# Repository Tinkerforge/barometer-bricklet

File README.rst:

Barometer Bricklet
==================

This repository contains the firmware source code and the hardware design
files. The documentation generator configs can be found at
https://github.com/Tinkerforge/generators

Repository Content
------------------

software/:
 * examples/: Examples for all supported languages
 * build/: Compiled files
 * src/: Source code of firmware
 * Makefile: Makefile to build project

hardware/:
 * Contains KiCad project files and additionally schematics as PDF

datasheets/:
 * Contains datasheets for sensors and complex ICs that are used

Hardware
--------

The hardware is designed with the open source EDA Suite KiCad
(http://www.kicad.org). Before you are able to open the files,
you have to install the Tinkerforge kicad-libraries
(https://github.com/Tinkerforge/kicad-libraries). You can either clone
them directly in hardware/ or clone them in a separate folder and
symlink them into hardware/
(ln -s kicad_path/kicad-libraries project_path/hardware). After that you
can open the .pro file in hardware/ with KiCad and from there view and
modify the schematics and the PCB layout.

Software
--------

If you want to do your own Brick/Bricklet firmware development we highly
recommend that you use our build environment setup script and read the
tutorial (https://www.tinkerforge.com/en/doc/Tutorials/Tutorial_Build_Environment/Tutorial.html).

To compile the C code we recommend you to install the newest GNU Arm Embedded
Toolchain (https://launchpad.net/gcc-arm-embedded/+download).
You also need to install bricklib (https://github.com/Tinkerforge/bricklib)
and brickletlib (https://github.com/Tinkerforge/brickletlib).

You can either clone it directly in software/src/ or clone it in a
separate folder and symlink it into software/src/
(ln -s bricklib_path/bricklib project_path/software/src/ and
ln -s brickletlib_path/brickletlib project_path/software/src/).
Finally make sure to have CMake installed
(http://www.cmake.org/cmake/resources/software.html).

After that you can build the firmware by invoking make in software/.
The firmware (.bin) can then be found in software/build/ and uploaded
with brickv (click button "Flashing" on start screen).

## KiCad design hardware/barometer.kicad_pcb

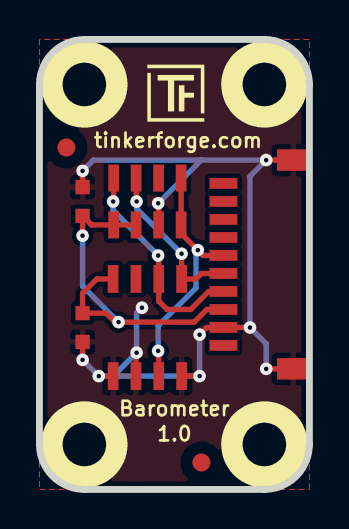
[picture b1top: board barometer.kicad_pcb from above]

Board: 2 copper layers, 15.0 x 25.0 mm, 13 parts (0 on the bottom side), 5 nets.

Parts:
C1, C2: 100nF; C0603
Fiducial_Mark: VAL**; Fiducial_Mark
Fiducial_Mark#2: VAL**; Fiducial_Mark
P1: CON-SENSOR
U1: M24C64; SOIC8
U2: MS5611
U3, U4, U5, U6: DRILL; DRILL_NP
VAL: CE_5mm
VAL#2: WEEE_7mm

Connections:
GND: C1.2, C2.2, P1.2, P1.EP, U1.1, U1.2, U1.4, U2.3
unnamed: P1.6, U1.3, U2.4, U2.5
SCL: P1.4, U1.6, U2.8
SDA: P1.5, U1.5, U2.7
VCC: C1.1, C2.1, P1.3, U1.8, U2.1, U2.2

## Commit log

2012-07-01 Add generate_makefile.bat for windows
2012-08-02 First try to implement calibration readout, not working yet
2012-08-03 Fix I2C communication and add calculation logic
2012-08-03 Remove Eclipse project files
2012-08-06 Apply moving average to air pressure
    Calculate air pressure with 5 extra bits of precision.
2012-08-10 Try to improve altitude calculation
    Simplify temperature to just a getter to make more RAM available.
    Add longer averaging for D1 and D2.
    Use a lookup table for altitude calculation.
2012-09-07 Ignore temporary build files
2012-09-17 update of hardware files
2012-09-28 Update to latest config
2012-09-28 Update datasheet
2012-09-28 Fix moving average calculation for D1 and fix auto calibration
2012-10-01 Replace calibate function with getter/setter for reference air pressure
    This is more flexible and allows to use QNH and QFE values.
2012-10-01 Check CRC4 of PROM data
2012-10-02 Add examples
2012-10-04 Extend .gitignore
2012-10-04 Fix overflow in altitude calculation
2012-10-04 Update changelog
2012-10-05 Update version number
    Missed in last commit.
2012-10-11 Fix sensor readout timings, avoids reading wrong sensor values
2012-10-24 Make cmake find the correct objcopy binary
    On some systems cmake uses the wrong objcopy binary, tell it to use
    the correct one.
2012-11-13 Support for protocol 2.0
2012-11-28 Make python examples protocol 2.0 compatible
2012-11-29 Make Ruby examples Protocol 2.0 compatible
2012-11-29 Make C examples Protocol 2.0 compatible
2012-11-29 Make Java examples Protocol 2.0 compatible
2012-11-29 Make PHP examples Protocol 2.0 compatible
2012-11-29 Make Delphi/Pascal examples Protocol 2.0 compatible
2012-11-30 delphi: Remove unnecessary parentheses and call destructor again
2012-12-05 Add protocol 2.0 compatability to C# bindings
2012-12-06 Fix C examples
2012-12-11 Avoid g++ warnings about missing casts in C examples
2013-01-09 Use specific device object for callbacks
2013-01-17 Make Java examples compatible to new listener approach
2013-01-28 Update outdated comment in Java example
2013-02-07 Use IPconnection disconnect explicitly in examples
2013-02-18 Add Visual Basic .NET examples
2013-03-05 Fix schematic filename
2013-05-14 Add API for configuration of averaging parameters
2013-08-09 Add shell examples
2013-08-21 windows: Don't trigger a build in generate_makefile.bat
    Also use normal make instead of a special named one.
2013-09-23 Fix typo
2013-12-19 Fix wrong length for GetDebounce packet (through brickletlib)
2014-01-10 Add Perl examples
2014-01-15 php: Use const for constant values
2014-02-07 Add Mathematica examples
2014-02-10 perl: fixed namespace
2014-02-11 javascript: adding examples
2014-02-11 javascript: short exmaples
2014-02-18 javascript: examples fixed
2014-02-20 javascript: add html examples
2014-02-24 javascript: port 4280, startExample()
2014-02-28 javascript: Break long lines and cleanup whitespace
2014-03-05 Add LabVIEW examples
2014-03-06 labview: Add examples in LV2010 format
2014-03-25 matlab: add examples
2014-04-02 java: Unify constants style
2014-04-02 perl: Unify print style
2014-04-17 matlab: Adapt examples to new callback style
2014-04-17 matlab: Add parentheses to make pygments happy
2014-04-17 matlab: Fix string in Octave
2014-07-15 java: Replace System.console() usage with an Eclipse compatible pattern
2014-12-02 Use ReadLine instead of ReadKey for C# example
2015-02-13 vbnet: Use ReadLine instead of ReadKey
    Because ReadKey doesn't work with a pipe as stdin on the RED Brick.
2015-03-02 windows: Stop cmake from searching for mingw32-make.exe
    Using MinGW Makefiles as generator makes cmake search for mingw32-make.exe
    which might not be installed because GnuWin32's make.exe is used instead.
2015-03-26 update hardware files of barometer bricklet
2015-04-09 c: Whitespace
2015-06-24 javascript: Cleanup output creation
2015-07-23 Make JavaScript browser example textarea readonly
2015-07-27 Cleanup C/C++, C#, Java, Python and Ruby examples
2015-07-29 Reformat changelog
2015-08-07 Use full device class name in Python examples
2015-08-12 Fix minor warnings in C/C++ examples
2015-08-14 Cleanup Delphi examples
2015-08-18 Cleanup VB.NET examples
2015-08-19 Cleanup Perl examples
2015-08-21 Prefer printf over puts in C/C++ examples
2015-09-09 Duplicate cmake call to fix bug during cmake creation
2015-09-30 Generator based example cleanup
2015-11-12 matlab: Fix callback handling for R2014a
    http://undocumentedmatlab.com/blog/matlab-callbacks-for-java-events-in-r2014a
2015-11-25 Include date and commit into changelog
2016-05-18 c: Add missing device destroy call
2016-07-01 Make the change UID comment more explicit
2016-07-01 Whitespace
2017-04-13 csharp: Adapt example
2017-04-21 shell: Adapt example
2017-06-02 octave: Use javaObject instead of deprecated java_new
2017-08-01 Fix schematic symbols/markings/descriptions
2017-08-01 Add 3d information (final)
2017-08-01 PDF schematic: color instead of b/w
2017-08-01 Add 3d information (final); *.brd to *.kicad_pcb
2017-08-01 Add 3d model (*.step & *.FCStd)
2017-11-30 Update examples from generator
2017-12-07 mathematica: Also generate .nb files
2018-01-30 Update examples
2018-02-19 javascript: Close div tag correctly
2018-02-20 Cleanup KiCad libraries config
    Ensure LibDir=kicad-libraries and LibName1=tinkerforge.
    Remove special library.
2018-05-24 perl: Use strict in examples
2018-07-11 Add Makefile with docker support
2018-07-11 Remove obsolete generate_makefile scripts
2018-07-11 Update directory structure and build instructions
2018-09-14 Fix typo in example
2018-11-06 Add rust examples
2018-11-07 rust: Accept host names for ip connection, fix naming inconsistencies
2018-11-07 rust: Rename callback receivers.
2018-12-14 Add go examples.
2018-12-14 go: Fix printf parameters.
2018-12-18 go: Change import path.
2018-12-18 go: Change import path again.
2018-12-20 rust: Reformat examples.
2019-01-24 mqtt: Add examples.
2019-01-24 mqtt: Fix example header.
2019-01-24 mqtt: Remove executable bit in example permissions.
2019-01-24 go: Minor example fixes.
2019-01-24 mqtt: Minor example fixes.
2019-03-28 mqtt: Fix whitespace.
2019-08-22 c: Adapt to bindings changes
2019-11-22 Prefer hPa over mbar
2020-01-13 examples: Use python3 input instead of python2 raw_input.
2020-01-13 examples: mqtt: Remove trailing whitespace.
2020-05-04 Add get/set_i2c_mode. Mitigates EMI issues.
2020-05-04 Add commit ref to changelog.
2021-10-25 Update KiCad link
    https://www.kicad.org/blog/2021/10/Avoid-links-to-former-kicad-domain/
2022-07-06 Add license files.

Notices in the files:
hardware/barometer.kicad_pcb:
Licensed under CERN OHL v.1.1
Copyright (©) 2011, B.Nordmeyer
Copyright Tinkerforge GmbH 2011.
This documentation describes Open Hardware and is licensed under the
CERN OHL v. 1.1.
